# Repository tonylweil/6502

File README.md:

# DB6502 V2 Tony Weil's Updates  - 5/15/2020

KiCad Schematics, Board files and Gerbers in the Schematics/65C02_Computer directory have been updated to v002. In general, changes were made to add a sound chip and third VIA. Many jumpers were added allowing disconnecting and reconfiguring many signals. You can use jumpers to switch between LCD 4bit and 8bit wiring. See schematic for all changes.

Changes include:

Added VIA 3 6522

Added 76489 sound chip,  to VIA2, 4Mhz oscillator and Audio Jack

Added Port A and Port B female pin headers for all 3 VIAs

Jumpers on LCD to switch between BE6502 8 bit and DB6502 4 bit, Moved LCD connector to center of board

Jumpers for CPU: BE, SO, NMI, READY, Sync

Jumpers for ROM: /OE, /CE and /WE lines

Jumpers for RAM: /OE and /CE 

Jumpers for VIA1-3 and ACIA, A9-A12 and IOCS Chip Select lines to change hardware addressing

Jumper to ground ACIA /CTS line and FT230x /CTS to support no hardware handshaking

Jumpers added to disconnect any existing connections to VIA1 (LCD and ATTINY) and VIA2 (76489 Sound chip)

Jumpers to be able to use extra NOR gates

FT230X /RES connected to VCCIO with jumper so it doesn't reset USB when computer is reset

Moved Expansion header from center to edge of board

Reorder FTDI header to match dongles, add jumper to disconnect 5v power, changed to horizontal pin header, move to board edge

Changed USB Micro connector to USB Mini THT. Much easier to solder!

Delete USB-B

Added more mounting holes near VIAs and Expansion header to help with plugging in cables

# ==============================

# V1 Readme

# DB6502 - Dawid Buchwald's 6502 Computer

This repository contains all the work in progress during my build of Ben Eater's inspired 6502 8-bit computer similar to typical machines of the early 1980s. If you haven't seen Ben's videos, I would strongly suggest you start there:

[Ben Eater's 6502 project](https://eater.net/6502)

As stated above, this build is not 100% compatible with what Ben had done - and for a reason, described in next section.

If I had to explain shortly "what it is", the answer would be: simple, yet easy to expand, 8-bit CPU based computer designed and built with one goal only: to use it as a learning and tinkering platform to understand how computers really work. You can use it for simple things like understanding buses, clock cycles, instruction execution, but it also demonstrates more complex concepts like interrupts, interfaces to external components and device handling. More on that below. Everything, hopefully, is simple enough to wrap your head around by one person in couple of weeks.

## Why build something different

[Ben's videos](https://www.youtube.com/playlist?list=PLowKtXNTBypFbtuVMUVXNR0z1mu7dp7eH) on 6502 computer are absolutely awesome - it's one of the best sources in the whole Internet explaining how any computer works. The build he introduced is probably sufficient for most of the things you might ever want to build, and yet I decided to deviate from his design.

The rationale behind this project is pretty simple - the best way to test your understanding of certain subject is to try to expand on what you have learned. You never know if you understood something until you test it by introducing changes to original design - and I used this approach in this project to learn a lot. It was my first proper electronics project, so I would like to apologize for any mistakes. If you think something is off or could have been done differently - please go ahead and raise issue for the repo! All improvements are welcome!

## Why would you bother using DB6502 instead of BE6502

Basically, it gives you almost all the flexibility of Ben's buid without the hassle of breadboard connections for the critical components. You can still run all of Ben's programs (using second VIA port), but the days of looking for loose wire between RAM and CPU are over :) You can, obviously, still experiment with peripherals and breadboard connections using extension port and second VIA.

On top of that you get additional features like extra screen (via onboard connector), keyboard for more versatile input and finally all-in-one serial over USB terminal. You also get easy to use software ready to be installed on the machine to jumpstart your tinkering. When using bootloader you don't even have to flash the EEPROM more than once!

**Important note:** All of the content here is, and always will be open source and free to use, and I don't intend to make any profit out of it. The only way I get anything at all (and it's only small commission to be used for future PCBWay orders) is when you order my boards from PCBWay using the links posted below, but you are welcome to grab these gerber files and order the boards from another provider, or even from PCBWay, just by uploading gerbers to your account, if you don't want me to get the commission :)

## What is different

Compared to Ben's 6502 build I introduced the following changes:

1. Added [automatic power-up reset circuitry](Schematics/README.md#automatic-power-on-reset),
2. Changed [address decoder logic](Schematics/README.md#address-decoder-change) (**very important from compatibility perspective**),
3. Changed [LCD interface](Schematics/README.md#lcd-interface-change) from 8-bit to 4-bit (**very important from compatibility perspective**),
4. Added [additional VIA chip](Schematics/README.md#extra-via-chip) to provide easy expansion of the system,
5. Added [ACIA chip for serial communication](Schematics/README.md#extra-acia-chip-for-serial-communication),
6. Added (**optional - more on that later**) [USB-UART interface](Schematics/README.md#extra-usb-uart-interface-chip) for easy connectivity with PC,
7. Added [PS/2 keyboard port and ATtiny4313-based keyboard controller](Schematics/README.md#ps2-keyboard-interface-and-attiny4313-based-controller) to provide proper replacement for five pushbuttons in Ben's design,
8. Added [expansion port](Schematics/README.md#expansion-port) (not really deviation from Ben's build, save for one detail - unlike Ben's build, my version can support various interrupt sources, including the expansion port),
9. Modified [clock module](Schematics/README.md#modified-clock-module) (external),
10. Changed [compilator from VASM to CC65](Schematics/README.md#migration-from-vasm-to-cc65),
11. Added [simple way to choose clock source](Schematics/README.md#clock-input).

You might be wondering if this means that you can't run Ben's programs on DB6502 - and the answer is **YES YOU CAN**. Indeed, some changes to the code are necessary, but thanks to the additional VIA chip and with some changes to the addressing mode you can run any program from Ben's videos. If you want to use LCD in 8-bit mode, you can also use the additional VIA for it, ignoring the built-in LCD connector.

By the way, the opposite is also true - **you can compile and run my programs on Ben's computer**. There are special compilation flags that enable usage of Ben's address decoder. I will describe this in more detail in software section.

Detailed description and rationale for each change is discussed in [Schematics README](Schematics/README.md).

## Getting started

Okay, so it should be pretty clear what this project is about, so how to start playing with it? That really depends on what you decide to do:

- Stick with BE6502 and just use subset of provided software (either to install it in EEPROM, or just use it as reference for your own hacking),
- Build your own breadboard design based on this one with any modifications you can think of,
- Order PCBs of DB6502, solder the components and run provided software to see how it works and get started with your own designs.

To start from scratch it's actually easiest to select last option - after some waiting you will end up having pretty solid base to extend your design on.

### Using provided software with BE6502

If you decide to go down that route, head straight to the `Software` folder, where you will find several programs either identical or similar to what Ben has shown in his videos, but built with much more versatile toolchain.

If you want to read more, go ahead and read [Software folder](Software/README.md) section. Make sure to check out the [building software](Software/README.md#building-software) subsection, as it explains how to compile programs to run on BE6502 directly.

### Build your own breadboard design

Maybe you have already started expanding on Ben's build, or maybe you are just considering it now. If you want to check out how I did certain things, jump right into `Schematics` [folder](Schematics/README.md), where you will find KiCAD projects for all the components used in this project. Obviously the most important one is the `65C02_Computer` project, but there are some additional goodies there.

**Please note:** This part is not very well documented, I have assumed that anybody willing to dig into these schematics already knows how to read them.

Most of the decisions made during the schematic design were explained above. Justification for anything not covered here can be probably found in the [invaluable 6502 primer](http://wilsonminesco.com/6502primer/).

### Using my PCB design

This will be explained in the most detail, obviously. Start with getting [the PCBs](Schematics/README.md#ordering-pcb). **Please note:** clock module is entirely optional, but really useful for single stepping or slow clocking required by Ben Eater's design of Arduino Mega based bus analyzer. As explained in number of places here, you can either order PCBs from PCBWay directly or use your manufacturer of choice - it should have no impact on the final result.

## What's in the repo

Everything, basically. Schematics of the 6502 board, modified clock module, address decoder and other circuits I built during the project. Arduino sketches I used for debugging and simple programs used to test different features.

And, last but not least, full set of sample programs to follow Ben's videos on DB6502 plus my own bootloader/OS. The last two things are coming soon :)

### `Arduino` folder

There are several sketches there, and their full description is available is [separate README](Arduino/README.md).

### `Datasheets` folder

All the datasheets I used when designing DB6502, attached for reference.

### `Schematics` folder

All the KiCAD schematics for the 6502 computer, modified clock module and several others:

- 65C02_Computer - main schematic, including PCB design for DB6502 computer,
- Clock_module - schematic for the modified clock module, including PCB design,
- 555_troubleshoot - schematic of circuit used in [troubleshooting of clock module monostable noise issue](https://www.reddit.com/r/beneater/comments/edp1ls/noise_issue_in_monostable_mode_of_ben_eaters/),
- Address_decoder_basic - schematic of Ben Eater's address decoder for 6502 project,
- Address_decoder_basic_v2 - slightly modified version of the above,
- Address_decoder_extended - schematic of my own address decoder, used in the DB6502 computer.

There is dedicated [README](Schematics/README.md) in the folder, containing all the build-related details.

### `Software` folder

This one is the most important folder, as it contains range of different programs to play with the 6502 computer. Large subset of this programs can be built for Ben Eater's version of the 6502 computer without any changes. Some of them, however, use features available only in DB6502, like ACIA or keyboard connector. These can still be ran on Ben Eater's 6502 computer, assuming that compatible hardware is added to it.

The `Software` folder is currently divided into four main parts:

- `build` - temporary folder where all the build artifacts are created, including ROM binaries to be uploaded to EEPROM,
- `common` - common sources: include files with common constants, sources with shared function, configuration files for different address decoder logic modes, shared makefile used by all projects and small python script to optimize size of loadable modules,
- `rom` - set of projects used to create various ROM images to follow Ben's videos, test different features of the board and **some day** complete operating system for the computer,
- `load` - set of project containing loadable modules. These can be uploaded at runtime, without the need to flash the EEPROM. Basic bootloader is required, obviously, and the usage instructions are provided below.

There is also one "master" makefile located directly in the `Software` folder - it will build all the projects in `rom` and `load` subfolders.

There is dedicated [README](Software/README.md) in the folder, containing all the software-related details.

## Credits

This project would not be possible if not inspiration, support and help from many, many people:

- [Ben Eater](https://eater.net) - his videos inspired me to learn all this,
- [Dirk Grappendorf](https://grappendorf.net) - awesome documentation of his own 6502 project,
- [Wilson Mines Co.](http://wilsonminesco.com) - the best source of 6502-related information,
- [Dane Creek Photography](https://github.com/danecreekphotography) - for all his support and test driving the project,
- [u/transistorykris](https://www.reddit.com/user/transitorykris/) - his [KrisOS](https://github.com/transitorykris/krisos) is a great inspiration for my own OS development,
- [r/beneater community](https://www.reddit.com/r/beneater/) - for all the great ideas, feedback, creative spirit and exceptional support.

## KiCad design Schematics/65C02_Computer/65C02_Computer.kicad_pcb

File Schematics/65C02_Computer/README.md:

Schematics, PCB and Gerbers updates to v002

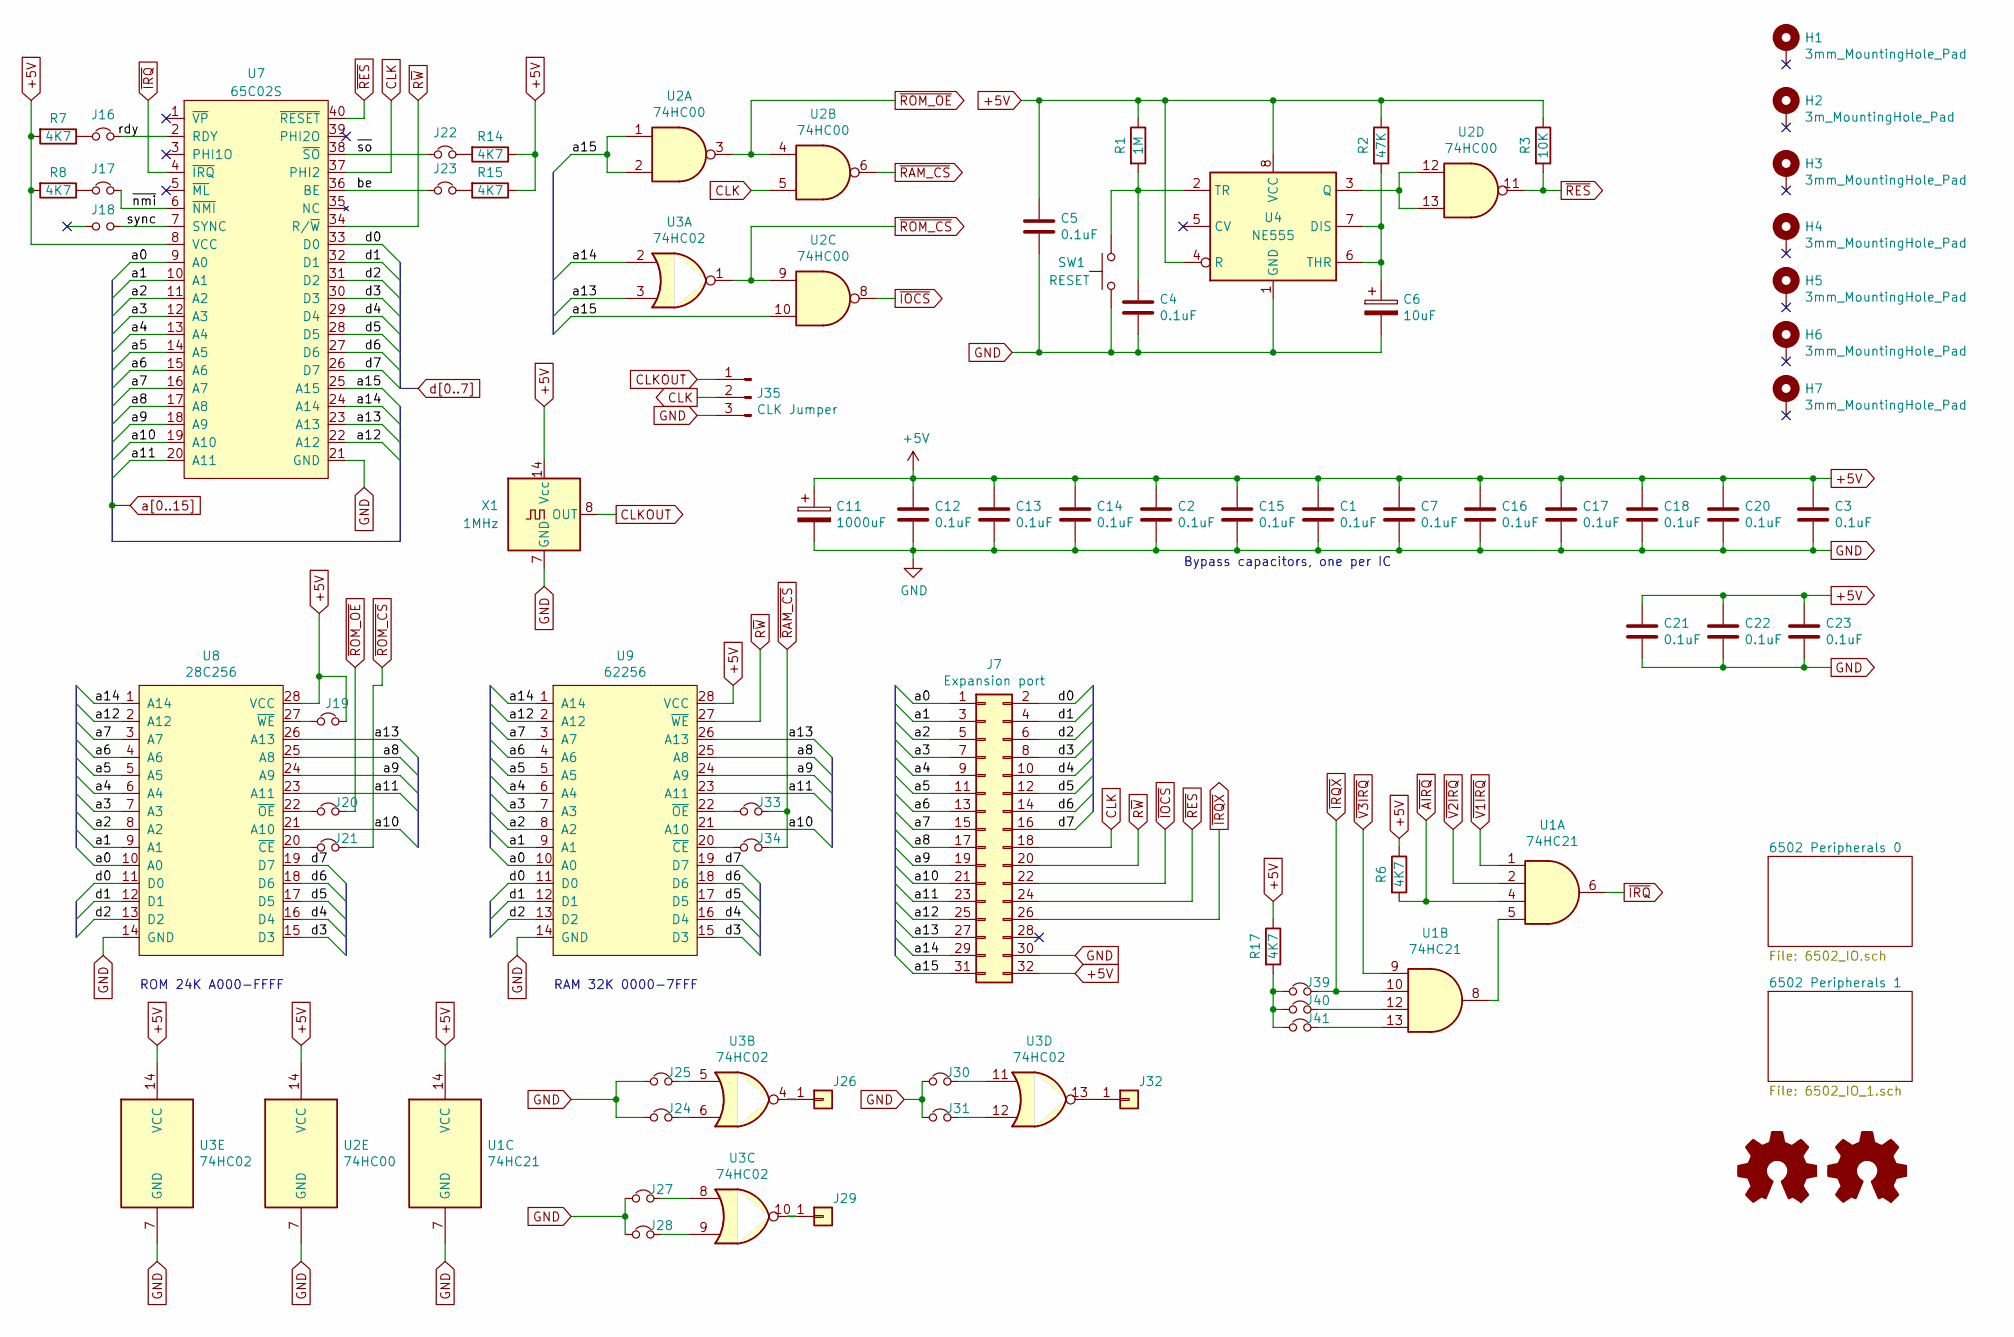
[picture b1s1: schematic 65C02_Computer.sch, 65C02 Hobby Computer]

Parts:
C1, C2, C3, C4, C5, C7, C12, C13, C14, C15, C16, C17, C18, C20, C21, C22, C23: 0.1uF; C_Disc_D3.4mm_W2.1mm_P2.50mm
C6: 10uF; CP_Radial_D5.0mm_P2.50mm
C11: 1000uF; CP_Radial_D10.0mm_P5.00mm
H1, H3, H4, H5, H6, H7: 3mm_MountingHole_Pad; MountingHole_3.2mm_Pad
H2: 3m_MountingHole_Pad; MountingHole_3.2mm_Pad
J7: Expansion port; PinSocket_2x16_P2.54mm_Vertical
J16, J17, J18, J22, J23, J39, J40, J41: J; PinHeader_1x02_P2.54mm_Vertical_Close
J19, J20, J21, J24, J25, J27, J28, J30, J31, J33, J34: Jumper_NC_Small; PinHeader_1x02_P2.54mm_Vertical_Close
J26, J29, J32: Conn_01x01; PinHeader_1x01_P2.54mm_Vertical_Close
J35: CLK Jumper; PinHeader_1x03_P2.54mm_Vertical_Close
LOGO1: Logo_Open_Hardware_Small; KiCad-Logo2_5mm_SilkScreen
LOGO2: Logo_Open_Hardware_Small; OSHW-Logo_5.7x6mm_SilkScreen
R1: 1M; R_Axial_DIN0207_L6.3mm_D2.5mm_P7.62mm_Horizontal
R2: 47K; R_Axial_DIN0207_L6.3mm_D2.5mm_P7.62mm_Horizontal
R3: 10K; R_Axial_DIN0207_L6.3mm_D2.5mm_P7.62mm_Horizontal
R6, R7, R8, R14, R15, R17: 4K7; R_Axial_DIN0207_L6.3mm_D2.5mm_P7.62mm_Horizontal
SW1: RESET; SW_PUSH_6mm_H4.3mm
U1: 74HC21; DIP-14_W7.62mm_Socket
U2: 74HC00; DIP-14_W7.62mm_Socket
U3: 74HC02; DIP-14_W7.62mm_Socket
U4: NE555; DIP-8_W7.62mm_Socket
U7: 65C02S; DIP-40_W15.24mm_Socket
U8: 28C256; DIP-28_W15.24mm_Socket
U9: 62256; DIP-28_W15.24mm_Socket
X1: 1MHz; Oscillator_DIP-14

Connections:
+5V: C1.1, C2.1, C3.1, C5.1, C7.1, C11.1, C12.1, C13.1, C14.1, C15.1, C16.1, C17.1, C18.1, C20.1, C21.1, C22.1, C23.1, J7.32, J19.2, R1.1, R2.1, R3.1, R6.1, R7.2, R8.2, R14.1, R15.1, R17.1, U1.14 (VCC), U2.14 (VCC), U3.14 (VCC), U4.4 (R), U4.8 (VCC), U7.8 (VCC), U8.28 (VCC), U9.28 (VCC), X1.14 (Vcc); also elsewhere on the board
/be: J23.1, U7.36 (BE)
/rdy: J16.2, U7.2 (RDY)
/sync: J18.2, U7.7 (SYNC)
/~nmi: J17.2, U7.6 (~NMI)
/~so: J22.1, U7.38 (~SO)
CLK: J7.18, J35.2, U2.5, U7.37 (PHI2); also elsewhere on the board
CLKOUT: J35.1, X1.8 (OUT)
GND: C1.2, C2.2, C3.2, C4.2, C5.2, C6.2, C7.2, C11.2, C12.2, C13.2, C14.2, C15.2, C16.2, C17.2, C18.2, C20.2, C21.2, C22.2, C23.2, J7.30, J24.1, J25.1, J27.1, J28.1, J30.1, J31.1, J35.3, SW1.1, U1.7 (GND), U2.7 (GND), U3.7 (GND), U4.1 (GND), U7.21 (GND), U8.14 (GND), U9.14 (GND), X1.7 (GND); also elsewhere on the board
unnamed: C4.1, R1.2, SW1.2, U4.2 (TR)
unnamed: C6.1, R2.2, U4.6 (THR), U4.7 (DIS)
unnamed: J16.1, R7.1
unnamed: J17.1, R8.1
unnamed: J19.1, U8.27 (~WE)
unnamed: J20.1, U8.22 (~OE)
unnamed: J21.1, U8.20 (~CE)
unnamed: J22.2, R14.2
unnamed: J23.2, R15.2
unnamed: J24.2, U3.6
unnamed: J25.2, U3.5
unnamed: J26.1, U3.4
unnamed: J27.2, U3.8
unnamed: J28.2, U3.9
unnamed: J29.1, U3.10
unnamed: J30.2, U3.11
unnamed: J31.2, U3.12
unnamed: J32.1, U3.13
unnamed: J33.1, U9.22 (~OE)
unnamed: J34.1, U9.20 (~CE)
unnamed: J39.1, J40.1, J41.1, R17.2
unnamed: J40.2, U1.12
unnamed: J41.2, U1.13
unnamed: U1.5, U1.8
unnamed: U2.12, U2.13, U4.3 (Q)
R~W: J7.20, U7.34 (R/~W), U9.27 (~WE); also elsewhere on the board
a0: J7.1, U7.9 (A0), U8.10 (A0), U9.10 (A0); also elsewhere on the board
a1: J7.3, U7.10 (A1), U8.9 (A1), U9.9 (A1); also elsewhere on the board
a2: J7.5, U7.11 (A2), U8.8 (A2), U9.8 (A2); also elsewhere on the board
a3: J7.7, U7.12 (A3), U8.7 (A3), U9.7 (A3); also elsewhere on the board
a4: J7.9, U7.13 (A4), U8.6 (A4), U9.6 (A4)
a5: J7.11, U7.14 (A5), U8.5 (A5), U9.5 (A5)
a6: J7.13, U7.15 (A6), U8.4 (A6), U9.4 (A6)
a7: J7.15, U7.16 (A7), U8.3 (A7), U9.3 (A7)
a8: J7.17, U7.17 (A8), U8.25 (A8), U9.25 (A8)
a9: J7.19, U7.18 (A9), U8.24 (A9), U9.24 (A9); also elsewhere on the board
a10: J7.21, U7.19 (A10), U8.21 (A10), U9.21 (A10); also elsewhere on the board
a11: J7.23, U7.20 (A11), U8.23 (A11), U9.23 (A11); also elsewhere on the board
a12: J7.25, U7.22 (A12), U8.2 (A12), U9.2 (A12); also elsewhere on the board
a13: J7.27, U3.3, U7.23 (A13), U8.26 (A13), U9.26 (A13)
a14: J7.29, U3.2, U7.24 (A14), U8.1 (A14), U9.1 (A14)
a15: J7.31, U2.1, U2.2, U2.10, U7.25 (A15)
d0: J7.2, U7.33 (D0), U8.11 (D0), U9.11 (D0); also elsewhere on the board
d1: J7.4, U7.32 (D1), U8.12 (D1), U9.12 (D1); also elsewhere on the board
d2: J7.6, U7.31 (D2), U8.13 (D2), U9.13 (D2); also elsewhere on the board
d3: J7.8, U7.30 (D3), U8.15 (D3), U9.15 (D3); also elsewhere on the board
d4: J7.10, U7.29 (D4), U8.16 (D4), U9.16 (D4); also elsewhere on the board
d5: J7.12, U7.28 (D5), U8.17 (D5), U9.17 (D5); also elsewhere on the board
d6: J7.14, U7.27 (D6), U8.18 (D6), U9.18 (D6); also elsewhere on the board
d7: J7.16, U7.26 (D7), U8.19 (D7), U9.19 (D7); also elsewhere on the board
~AIRQ: R6.2, U1.4; also elsewhere on the board
~IOCS: J7.22, U2.8; also elsewhere on the board
~IRQ: U1.6, U7.4 (~IRQ)
~IRQX: J7.26, J39.2, U1.10
~RAM_CS: J33.2, J34.2, U2.6
~RES: J7.24, R3.2, U2.11, U7.40 (~RESET); also elsewhere on the board
~ROM_CS: J21.2, U2.9, U3.1
~ROM_OE: J20.2, U2.3, U2.4
~V1IRQ: U1.1; also elsewhere on the board
~V2IRQ: U1.2; also elsewhere on the board
~V3IRQ: U1.9; also elsewhere on the board

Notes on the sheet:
ROM 24K A000-FFFF
RAM 32K 0000-7FFF
Bypass capacitors, one per IC

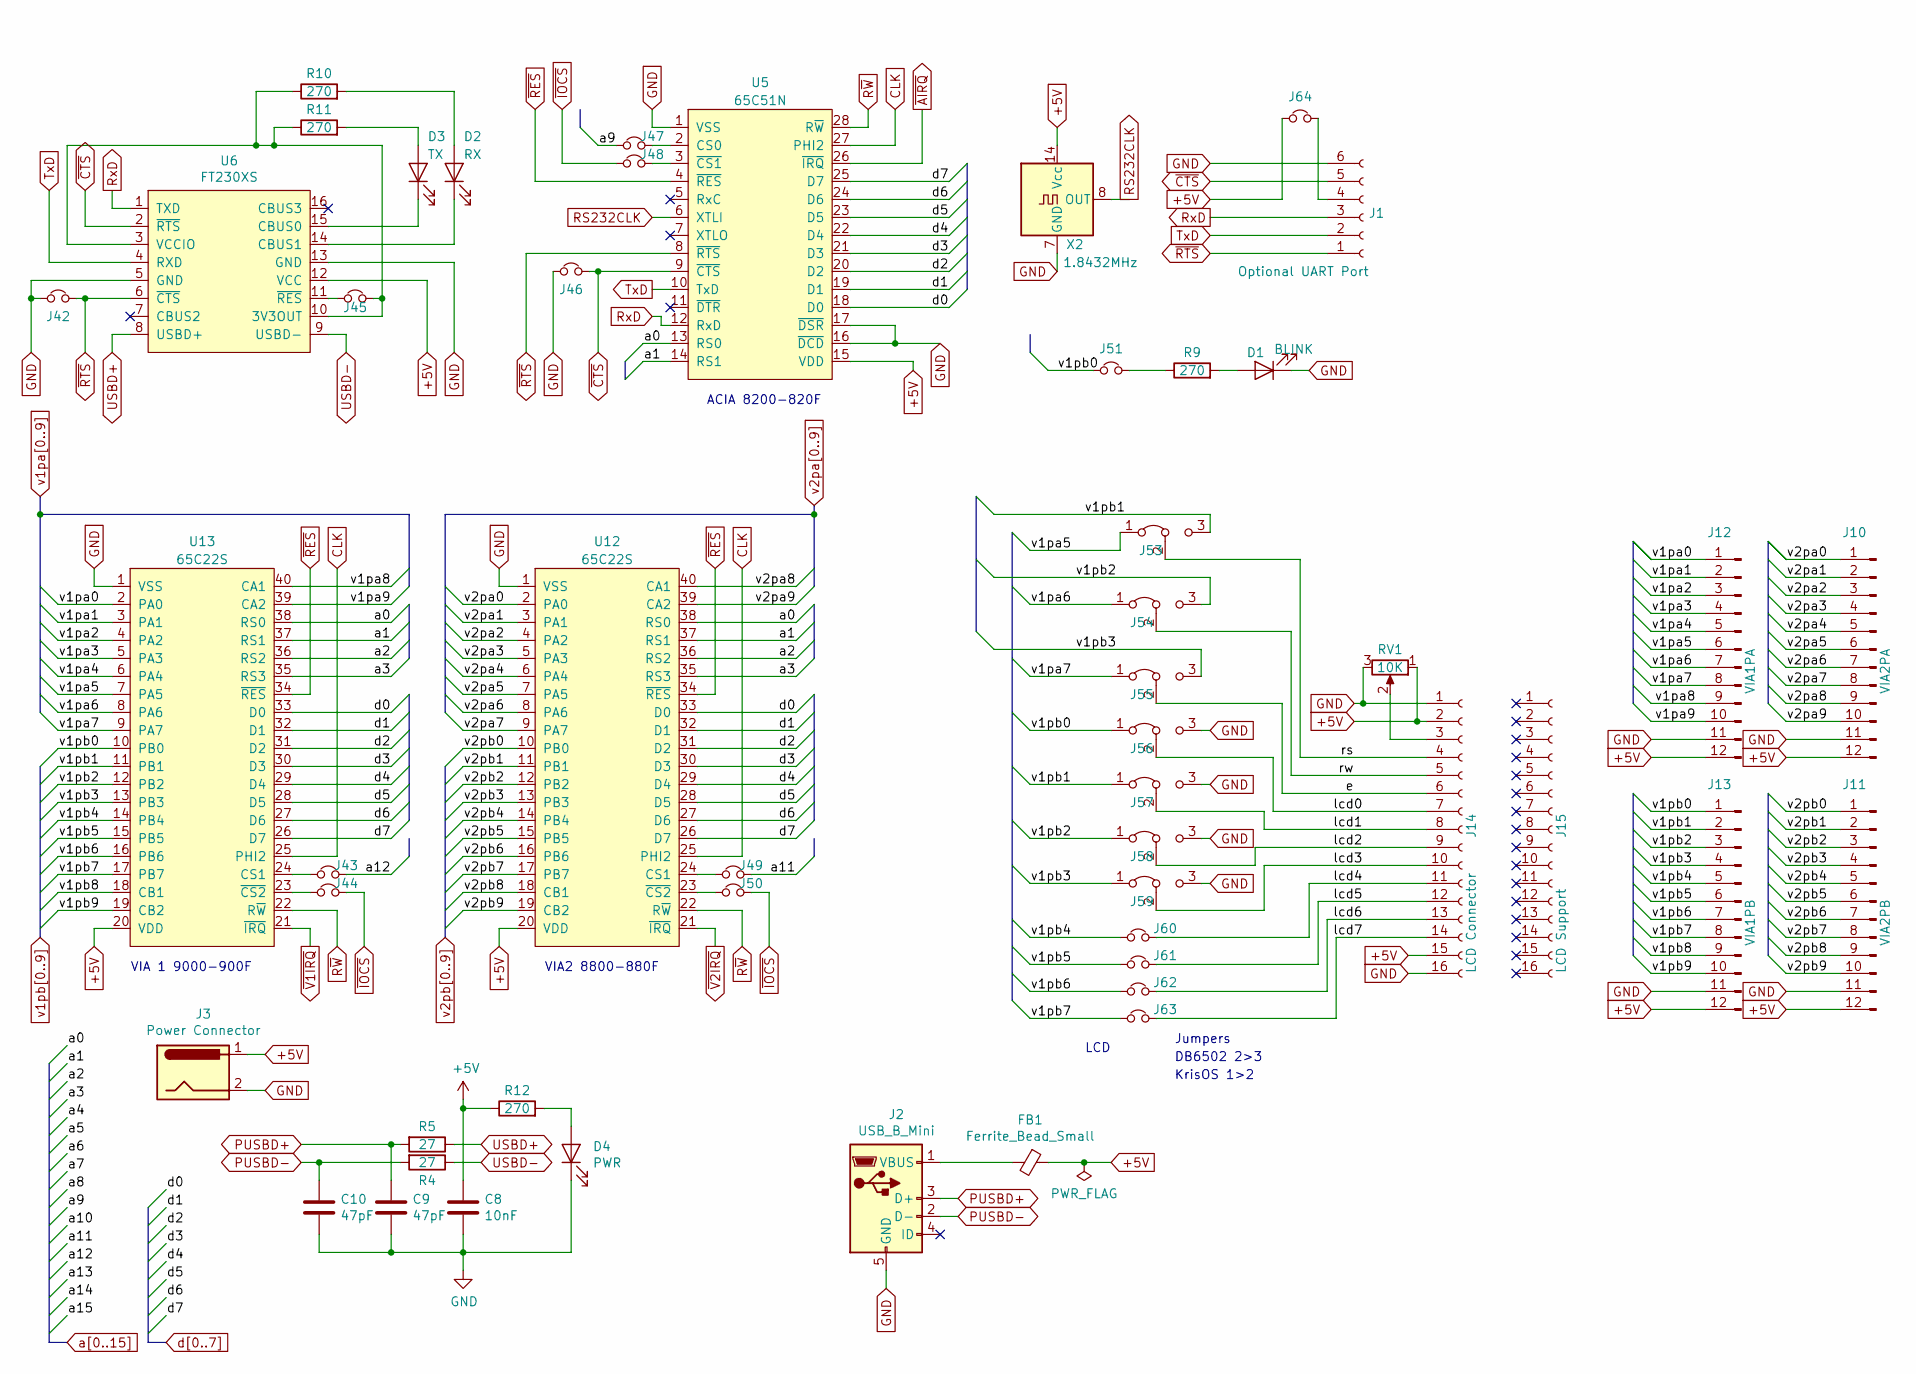
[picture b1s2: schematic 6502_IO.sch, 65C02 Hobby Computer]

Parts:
C8: 10nF; C_Disc_D3.4mm_W2.1mm_P2.50mm
C9, C10: 47pF; C_Disc_D3.4mm_W2.1mm_P2.50mm
D1: BLINK; LED_D5.0mm_Clear
D2: RX; LED_D5.0mm_Clear
D3: TX; LED_D5.0mm_Clear
D4: PWR; LED_D5.0mm_Clear
FB1: Ferrite_Bead_Small; R_Axial_DIN0207_L6.3mm_D2.5mm_P7.62mm_Horizontal
J1: Optional UART Port; PinSocket_1x06_P2.54mm_Horizontal
J2: USB_B_Mini; USB-MINI-B-PTH-1734510
J3: Power Connector; BarrelJack_Horizontal
J10: VIA2PA; PinSocket_1x12_P2.54mm_Vertical
J11: VIA2PB; PinSocket_1x12_P2.54mm_Vertical
J12: VIA1PA; PinSocket_1x12_P2.54mm_Vertical
J13: VIA1PB; PinSocket_1x12_P2.54mm_Vertical
J14: LCD Connector; LCD-4line
J15: LCD Support; PinSocket_1x16_P2.54mm_Vertical
J42, J43, J44, J45, J47, J48, J49, J50, J51, J60, J61, J62, J63, J64: Jumper_NC_Small; PinHeader_1x02_P2.54mm_Vertical_Close
J46: Jumper_NC_Small; PinHeader_1x02_P2.54mm_Vertical
J53, J54, J55, J56, J57, J58, J59: Jumper_3_Bridged12; PinHeader_1x03_P2.54mm_Vertical_Close
R4, R5: 27; R_Axial_DIN0207_L6.3mm_D2.5mm_P7.62mm_Horizontal
R9, R10, R11, R12: 270; R_Axial_DIN0207_L6.3mm_D2.5mm_P7.62mm_Horizontal
RV1: 10K; Potentiometer_Piher_PT-6-V_Vertical
U5: 65C51N; DIP-28_W15.24mm_Socket
U6: FT230XS; SSOP-16_3.9x4.9mm_P0.635mm_long_pads
U12, U13: 65C22S; DIP-40_W15.24mm_Socket
X2: 1.8432MHz; Oscillator_DIP-14

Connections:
+5V: C8.1, FB1.1, J3.1, J10.12, J11.12, J12.12, J13.12, J14.2, J14.15, J64.1, R12.1, RV1.1, U5.15 (VDD), U6.12 (VCC), U12.20 (VDD), U13.20 (VDD), X2.14 (Vcc); also elsewhere on the board
/6502 Peripherals 0/e: J14.6, J55.2 (C)
/6502 Peripherals 0/lcd0: J14.7, J56.2 (C)
/6502 Peripherals 0/lcd1: J14.8, J57.2 (C)
/6502 Peripherals 0/lcd2: J14.9, J58.2 (C)
/6502 Peripherals 0/lcd3: J14.10, J59.2 (C)
/6502 Peripherals 0/lcd4: J14.11, J60.2
/6502 Peripherals 0/lcd5: J14.12, J61.2
/6502 Peripherals 0/lcd6: J14.13, J62.2
/6502 Peripherals 0/lcd7: J14.14, J63.2
/6502 Peripherals 0/rs: J14.4, J53.2 (C)
/6502 Peripherals 0/rw: J14.5, J54.2 (C)
CLK: U5.27 (PHI2), U12.25 (PHI2), U13.25 (PHI2); also elsewhere on the board
GND: C8.2, C9.2, C10.2, D1.1 (K), D4.1 (K), J1.6, J2.5 (GND), J3.2, J10.11, J11.11, J12.11, J13.11, J14.1, J14.16, J42.1, J46.1, J56.3 (B), J57.3 (B), J58.3 (B), J59.3 (B), RV1.3, U5.1 (VSS), U5.16 (~DCD), U5.17 (~DSR), U6.5 (GND), U6.13 (GND), U12.1 (VSS), U13.1 (VSS), X2.7 (GND); also elsewhere on the board
unnamed: D1.2 (A), R9.2
unnamed: D2.1 (K), U6.14 (CBUS1)
unnamed: D2.2 (A), R10.2
unnamed: D3.1 (K), U6.15 (CBUS0)
unnamed: D3.2 (A), R11.2
unnamed: D4.2 (A), R12.2
unnamed: FB1.2, J2.1 (VBUS)
unnamed: J1.4, J64.2
unnamed: J14.3, RV1.2
unnamed: J43.1, U13.24 (CS1)
unnamed: J44.1, U13.23 (~CS2)
unnamed: J45.1, U6.11 (~RES)
unnamed: J45.2, R10.1, R11.1, U6.3 (VCCIO), U6.10 (3V3OUT)
unnamed: J47.2, U5.2 (CS0)
unnamed: J48.2, U5.3 (~CS1)
unnamed: J49.1, U12.24 (CS1)
unnamed: J50.1, U12.23 (~CS2)
unnamed: J51.2, R9.1
PUSBD+: C9.1, J2.3 (D+), R5.2
PUSBD-: C10.1, J2.2 (D-), R4.2
RS232CLK: U5.6 (XTLI), X2.8 (OUT)
RxD: J1.3, U5.12 (RxD), U6.1 (TXD)
R~W: U5.28 (R~W), U12.22 (R~W), U13.22 (R~W); also elsewhere on the board
TxD: J1.2, U5.10 (TxD), U6.4 (RXD)
USBD+: R5.1, U6.8 (USBD+)
USBD-: R4.1, U6.9 (USBD-)
a0: U5.13 (RS0), U12.38 (RS0), U13.38 (RS0); also elsewhere on the board
a1: U5.14 (RS1), U12.37 (RS1), U13.37 (RS1); also elsewhere on the board
a2: U12.36 (RS2), U13.36 (RS2); also elsewhere on the board
a3: U12.35 (RS3), U13.35 (RS3); also elsewhere on the board
a9: J47.1; also elsewhere on the board
a11: J49.2; also elsewhere on the board
a12: J43.2; also elsewhere on the board
d0: U5.18 (D0), U12.33 (D0), U13.33 (D0); also elsewhere on the board
d1: U5.19 (D1), U12.32 (D1), U13.32 (D1); also elsewhere on the board
d2: U5.20 (D2), U12.31 (D2), U13.31 (D2); also elsewhere on the board
d3: U5.21 (D3), U12.30 (D3), U13.30 (D3); also elsewhere on the board
d4: U5.22 (D4), U12.29 (D4), U13.29 (D4); also elsewhere on the board
d5: U5.23 (D5), U12.28 (D5), U13.28 (D5); also elsewhere on the board
d6: U5.24 (D6), U12.27 (D6), U13.27 (D6); also elsewhere on the board
d7: U5.25 (D7), U12.26 (D7), U13.26 (D7); also elsewhere on the board
v1pa0: J12.1, U13.2 (PA0); also elsewhere on the board
v1pa1: J12.2, U13.3 (PA1); also elsewhere on the board
v1pa2: J12.3, U13.4 (PA2); also elsewhere on the board
v1pa3: J12.4, U13.5 (PA3); also elsewhere on the board
v1pa4: J12.5, U13.6 (PA4); also elsewhere on the board
v1pa5: J12.6, J53.1 (A), U13.7 (PA5); also elsewhere on the board
v1pa6: J12.7, J54.1 (A), U13.8 (PA6); also elsewhere on the board
v1pa7: J12.8, J55.1 (A), U13.9 (PA7); also elsewhere on the board
v1pa8: J12.9, U13.40 (CA1); also elsewhere on the board
v1pa9: J12.10, U13.39 (CA2); also elsewhere on the board
v1pb0: J13.1, J51.1, J56.1 (A), U13.10 (PB0)
v1pb1: J13.2, J53.3 (B), J57.1 (A), U13.11 (PB1)
v1pb2: J13.3, J54.3 (B), J58.1 (A), U13.12 (PB2)
v1pb3: J13.4, J55.3 (B), J59.1 (A), U13.13 (PB3)
v1pb4: J13.5, J60.1, U13.14 (PB4)
v1pb5: J13.6, J61.1, U13.15 (PB5)
v1pb6: J13.7, J62.1, U13.16 (PB6)
v1pb7: J13.8, J63.1, U13.17 (PB7)
v1pb8: J13.9, U13.18 (CB1)
v1pb9: J13.10, U13.19 (CB2)
v2pa0: J10.1, U12.2 (PA0)
v2pa1: J10.2, U12.3 (PA1)
v2pa2: J10.3, U12.4 (PA2)
v2pa3: J10.4, U12.5 (PA3)
v2pa4: J10.5, U12.6 (PA4)
v2pa5: J10.6, U12.7 (PA5)
v2pa6: J10.7, U12.8 (PA6); also elsewhere on the board
v2pa7: J10.8, U12.9 (PA7); also elsewhere on the board
v2pa8: J10.9, U12.40 (CA1)
v2pa9: J10.10, U12.39 (CA2)
v2pb0: J11.1, U12.10 (PB0); also elsewhere on the board
v2pb1: J11.2, U12.11 (PB1); also elsewhere on the board
v2pb2: J11.3, U12.12 (PB2); also elsewhere on the board
v2pb3: J11.4, U12.13 (PB3); also elsewhere on the board
v2pb4: J11.5, U12.14 (PB4); also elsewhere on the board
v2pb5: J11.6, U12.15 (PB5); also elsewhere on the board
v2pb6: J11.7, U12.16 (PB6); also elsewhere on the board
v2pb7: J11.8, U12.17 (PB7); also elsewhere on the board
v2pb8: J11.9, U12.18 (CB1)
v2pb9: J11.10, U12.19 (CB2)
~AIRQ: U5.26 (~IRQ); also elsewhere on the board
~CTS: J1.5, J46.2, U5.9 (~CTS), U6.2 (~RTS)
~IOCS: J44.2, J48.1, J50.2; also elsewhere on the board
~RES: U5.4 (~RES), U12.34 (~RES), U13.34 (~RES); also elsewhere on the board
~RTS: J1.1, J42.2, U5.8 (~RTS), U6.6 (~CTS)
~V1IRQ: U13.21 (~IRQ); also elsewhere on the board
~V2IRQ: U12.21 (~IRQ); also elsewhere on the board

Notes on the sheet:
DB6502 2>3
KrisOS 1>2
Jumpers
LCD
VIA 1 9000-900F
VIA2 8800-880F
ACIA 8200-820F

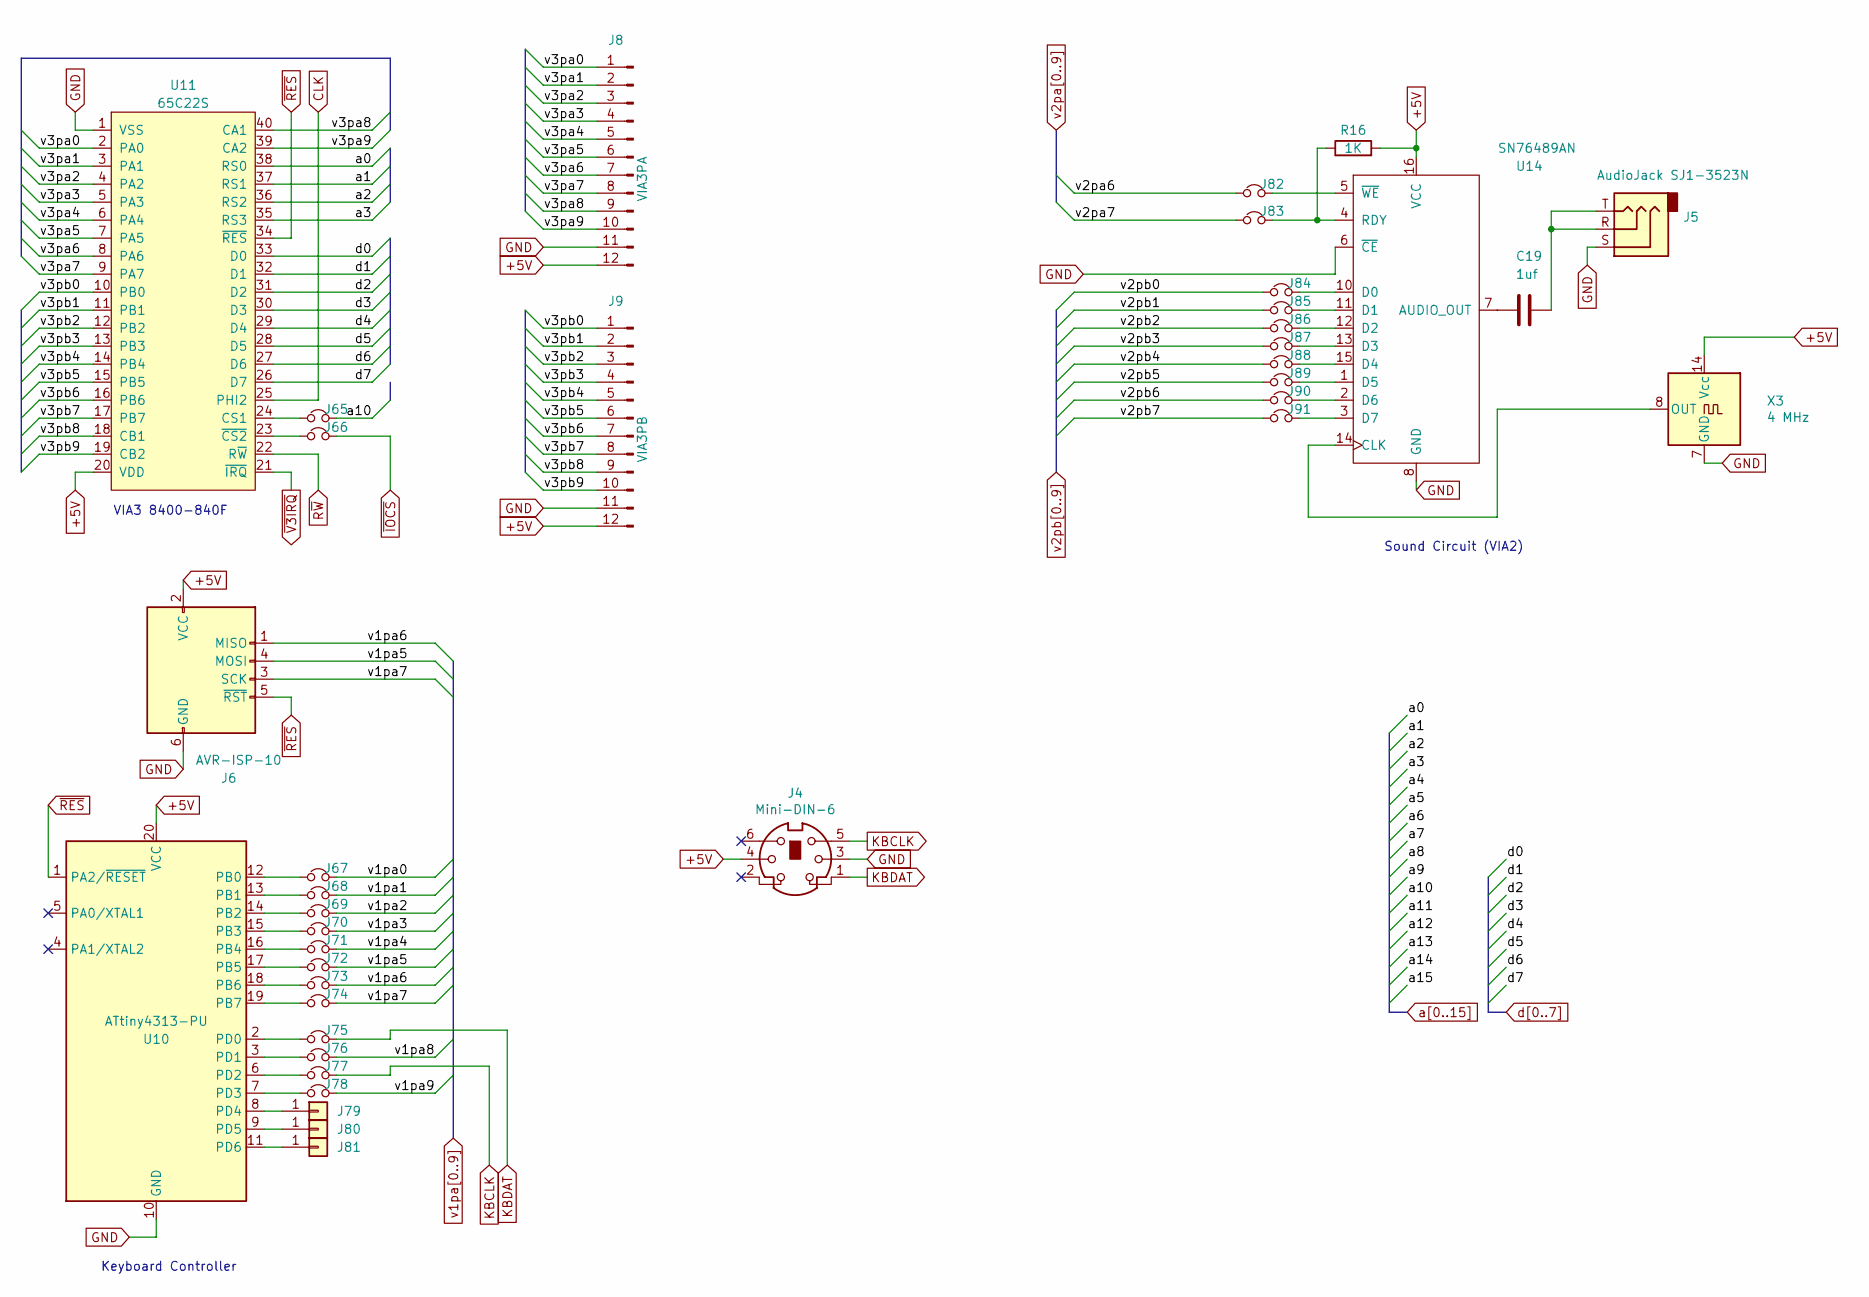
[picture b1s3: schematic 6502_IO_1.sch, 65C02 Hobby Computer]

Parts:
C19: 1uf; C_Disc_D3.4mm_W2.1mm_P2.50mm
J4: Mini-DIN-6; mini_din-6
J5: AudioJack SJ1-3523N; Jack_3.5mm_CUI_SJ1-3523N_Horizontal
J6: AVR-ISP-10; PinHeader_2x03_P2.54mm_Vertical
J8: VIA3PA; PinSocket_1x12_P2.54mm_Vertical
J9: VIA3PB; PinSocket_1x12_P2.54mm_Vertical
J65, J66, J67, J68, J69, J70, J71, J72, J73, J74, J75, J76, J77, J78, J82, J83, J84, J85, J86, J87, J88, J89, J90, J91: Jumper_NC_Small; PinHeader_1x02_P2.54mm_Vertical_Close
J79, J80, J81: Conn_01x01; PinHeader_1x01_P2.54mm_Vertical_Close
R16: 1K; R_Axial_DIN0207_L6.3mm_D2.5mm_P7.62mm_Horizontal
U10: ATtiny4313-PU; DIP-20_W7.62mm_Socket
U11: 65C22S; DIP-40_W15.24mm_Socket
U14: SN76489AN; DIP-16_W7.62mm_Socket
X3: 4 MHz; Oscillator_DIP-14

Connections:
+5V: J4.4, J6.2 (VCC), J8.12, J9.12, R16.2, U10.20 (VCC), U11.20 (VDD), U14.16 (VCC), X3.14 (Vcc); also elsewhere on the board
/6502 Peripherals 1/v3pa0: J8.1, U11.2 (PA0)
/6502 Peripherals 1/v3pa1: J8.2, U11.3 (PA1)
/6502 Peripherals 1/v3pa2: J8.3, U11.4 (PA2)
/6502 Peripherals 1/v3pa3: J8.4, U11.5 (PA3)
/6502 Peripherals 1/v3pa4: J8.5, U11.6 (PA4)
/6502 Peripherals 1/v3pa5: J8.6, U11.7 (PA5)
/6502 Peripherals 1/v3pa6: J8.7, U11.8 (PA6)
/6502 Peripherals 1/v3pa7: J8.8, U11.9 (PA7)
/6502 Peripherals 1/v3pa8: J8.9, U11.40 (CA1)
/6502 Peripherals 1/v3pa9: J8.10, U11.39 (CA2)
/6502 Peripherals 1/v3pb0: J9.1, U11.10 (PB0)
/6502 Peripherals 1/v3pb1: J9.2, U11.11 (PB1)
/6502 Peripherals 1/v3pb2: J9.3, U11.12 (PB2)
/6502 Peripherals 1/v3pb3: J9.4, U11.13 (PB3)
/6502 Peripherals 1/v3pb4: J9.5, U11.14 (PB4)
/6502 Peripherals 1/v3pb5: J9.6, U11.15 (PB5)
/6502 Peripherals 1/v3pb6: J9.7, U11.16 (PB6)
/6502 Peripherals 1/v3pb7: J9.8, U11.17 (PB7)
/6502 Peripherals 1/v3pb8: J9.9, U11.18 (CB1)
/6502 Peripherals 1/v3pb9: J9.10, U11.19 (CB2)
CLK: U11.25 (PHI2); also elsewhere on the board
GND: J4.3, J5.S, J6.6 (GND), J8.11, J9.11, U10.10 (GND), U11.1 (VSS), U14.6 (~CE), U14.8 (GND), X3.7 (GND); also elsewhere on the board
KBCLK: J4.5, J77.2
KBDAT: J4.1, J75.2
unnamed: C19.1, J5.R, J5.T
unnamed: C19.2, U14.7 (AUDIO_OUT)
unnamed: J65.1, U11.24 (CS1)
unnamed: J66.1, U11.23 (~CS2)
unnamed: J67.1, U10.12 (PB0)
unnamed: J68.1, U10.13 (PB1)
unnamed: J69.1, U10.14 (PB2)
unnamed: J70.1, U10.15 (PB3)
unnamed: J71.1, U10.16 (PB4)
unnamed: J72.1, U10.17 (PB5)
unnamed: J73.1, U10.18 (PB6)
unnamed: J74.1, U10.19 (PB7)
unnamed: J75.1, U10.2 (PD0)
unnamed: J76.1, U10.3 (PD1)
unnamed: J77.1, U10.6 (PD2)
unnamed: J78.1, U10.7 (PD3)
unnamed: J79.1, U10.8 (PD4)
unnamed: J80.1, U10.9 (PD5)
unnamed: J81.1, U10.11 (PD6)
unnamed: J82.2, U14.5 (~WE)
unnamed: J83.2, R16.1, U14.4 (RDY)
unnamed: J84.2, U14.10 (D0)
unnamed: J85.2, U14.11 (D1)
unnamed: J86.2, U14.12 (D2)
unnamed: J87.2, U14.13 (D3)
unnamed: J88.2, U14.15 (D4)
unnamed: J89.2, U14.1 (D5)
unnamed: J90.2, U14.2 (D6)
unnamed: J91.2, U14.3 (D7)
unnamed: U14.14 (CLK), X3.8 (OUT)
R~W: U11.22 (R~W); also elsewhere on the board
a0: U11.38 (RS0); also elsewhere on the board
a1: U11.37 (RS1); also elsewhere on the board
a2: U11.36 (RS2); also elsewhere on the board
a3: U11.35 (RS3); also elsewhere on the board
a10: J65.2; also elsewhere on the board
d0: U11.33 (D0); also elsewhere on the board
d1: U11.32 (D1); also elsewhere on the board
d2: U11.31 (D2); also elsewhere on the board
d3: U11.30 (D3); also elsewhere on the board
d4: U11.29 (D4); also elsewhere on the board
d5: U11.28 (D5); also elsewhere on the board
d6: U11.27 (D6); also elsewhere on the board
d7: U11.26 (D7); also elsewhere on the board
v1pa0: J67.2; also elsewhere on the board
v1pa1: J68.2; also elsewhere on the board
v1pa2: J69.2; also elsewhere on the board
v1pa3: J70.2; also elsewhere on the board
v1pa4: J71.2; also elsewhere on the board
v1pa5: J6.4 (MOSI), J72.2; also elsewhere on the board
v1pa6: J6.1 (MISO), J73.2; also elsewhere on the board
v1pa7: J6.3 (SCK), J74.2; also elsewhere on the board
v1pa8: J76.2; also elsewhere on the board
v1pa9: J78.2; also elsewhere on the board
v2pa6: J82.1; also elsewhere on the board
v2pa7: J83.1; also elsewhere on the board
v2pb0: J84.1; also elsewhere on the board
v2pb1: J85.1; also elsewhere on the board
v2pb2: J86.1; also elsewhere on the board
v2pb3: J87.1; also elsewhere on the board
v2pb4: J88.1; also elsewhere on the board
v2pb5: J89.1; also elsewhere on the board
v2pb6: J90.1; also elsewhere on the board
v2pb7: J91.1; also elsewhere on the board
~IOCS: J66.2; also elsewhere on the board
~RES: J6.5 (~RST), U10.1 (PA2/~RESET), U11.34 (~RES); also elsewhere on the board
~V3IRQ: U11.21 (~IRQ); also elsewhere on the board

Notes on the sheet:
Keyboard Controller
VIA3 8400-840F
Sound Circuit (VIA2)
